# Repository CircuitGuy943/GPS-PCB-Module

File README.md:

# GPS-PCB-Module
I needed a simple, but effective GPS capable PCB to accompany my Flight Controller on my drone and I decided to use the large flat area on top to utilise as much ground area as I could, because more ground area means better reception. So I made this PCB which maximises that area and provides me with an FPC connector which I can then attach to the main FC PCB and so use the GPS functionality.

## Features:
- Powerful L80RE-M37 GPS module combined with a ginormous ground plane for good reception.
- CR2032 cell battery holder for keeping time and reducing setup configuration needed
- 6-pin FPC carrying 3.3V power and UART connection to the MCU (not on this board)

## PCB
This is the PCB, simple double sided with cool silkscreen designs on top.

## Schematic
And here is the schematic too:

## 3D renders
Here are also some 3D renders done in Fusion and KiCad to show off the PCB :)

## Firmware Overview
I've also included some basic firmware (**untested**) that should get the GPS module working with the UART connected to an MCU.

## BOM:
The BOM file with the prices is also found in the root directory.

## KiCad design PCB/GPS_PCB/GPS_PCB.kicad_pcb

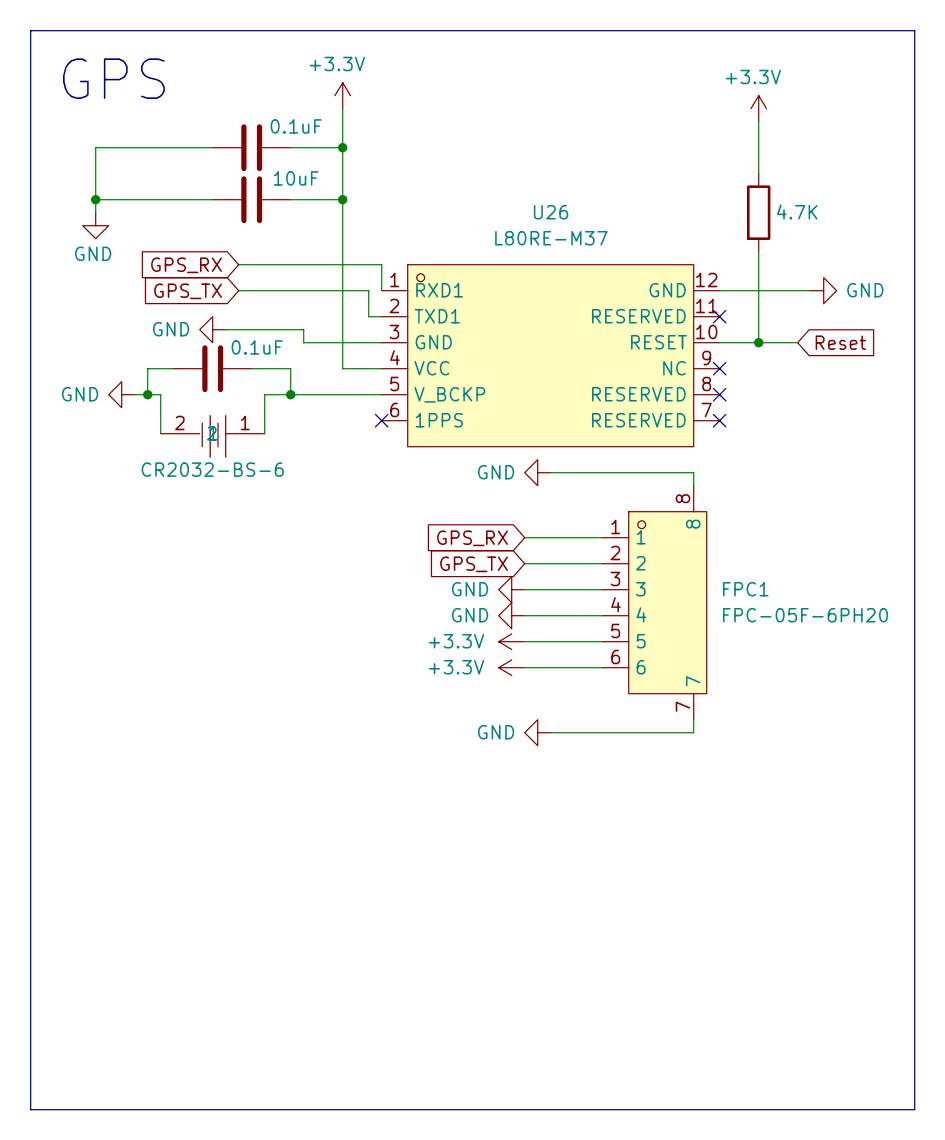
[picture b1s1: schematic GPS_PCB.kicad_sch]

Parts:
C79, C80: 0.1uF; C_0603_1608Metric
C120: 10uF; C_1206_3216Metric
FPC1: FPC-05F-6PH20; FPC-SMD_6P-P0.50_XUNPU_FPC-05F-6PH20; LCSC Part C2856796
R1: 4.7K; R_0603_1608Metric
U1: CR2032-BS-6; BAT-TH_CR2032-BS-6-1; LCSC Part C22363833
U26: L80RE-M37; GPSM-SMD_12P-L16.0-W16.0-P2.54-BL; LCSC Part C3029061

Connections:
+3.3V: C80.2, C120.2, FPC1.5, FPC1.6, R1.1, U26.4 (VCC)
GND: C79.1, C80.1, C120.1, FPC1.3, FPC1.4, FPC1.7, FPC1.8, U1.2, U26.3 (GND), U26.12 (GND)
GPS_RX: FPC1.1, U26.1 (RXD1)
GPS_TX: FPC1.2, U26.2 (TXD1)
unnamed: C79.2, U1.1, U26.5 (V_BCKP)
Reset: R1.2, U26.10 (RESET)

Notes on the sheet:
GPS

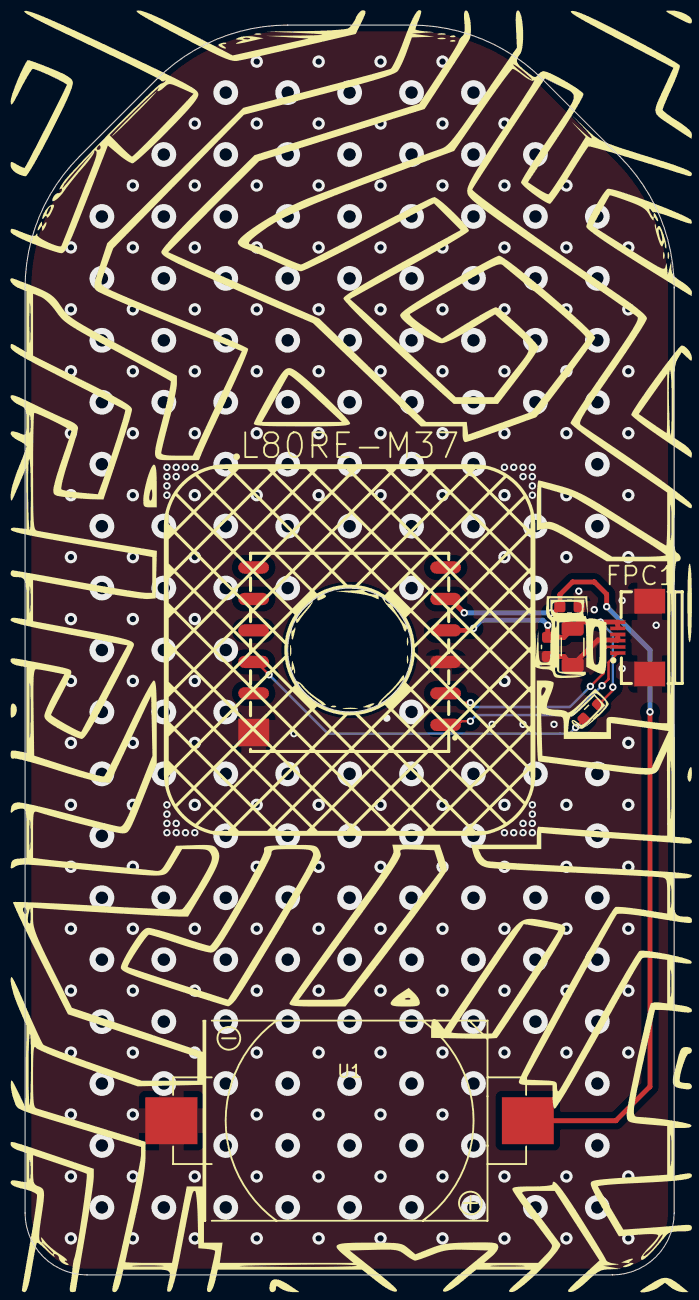
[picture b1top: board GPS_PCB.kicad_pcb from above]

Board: 2 copper layers, 52.4 x 100.9 mm, 7 parts (0 on the bottom side), 6 nets.

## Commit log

2026-03-08 Add main files
2026-03-28 Enhance README with detailed project information
    Expanded the README to include detailed features, PCB description, schematic, 3D renders, firmware overview, and BOM information.
